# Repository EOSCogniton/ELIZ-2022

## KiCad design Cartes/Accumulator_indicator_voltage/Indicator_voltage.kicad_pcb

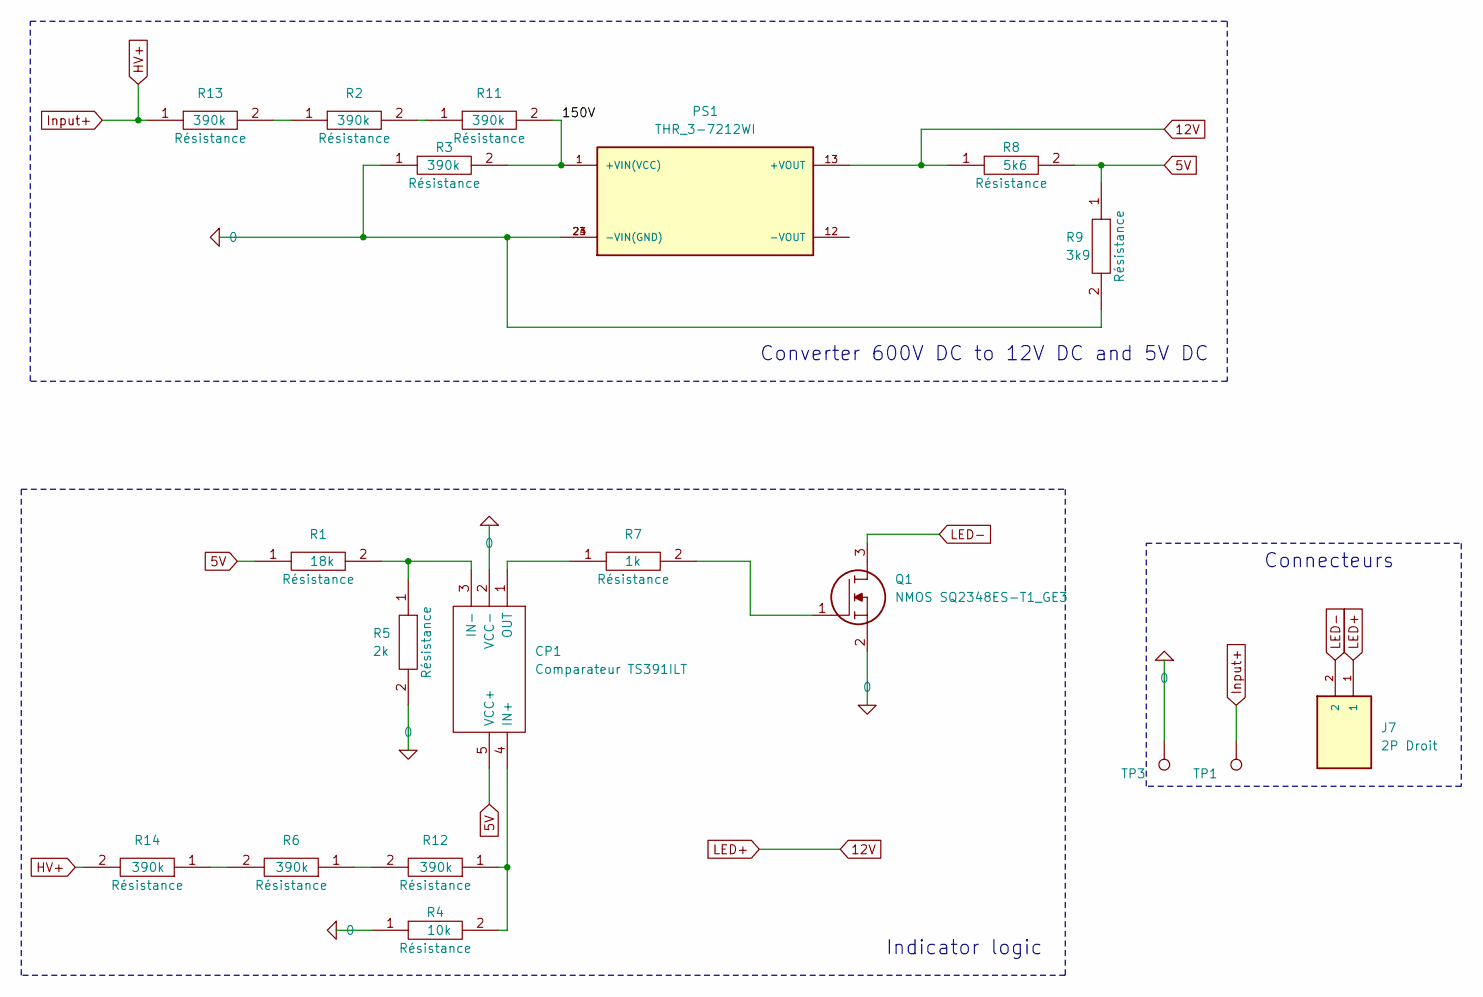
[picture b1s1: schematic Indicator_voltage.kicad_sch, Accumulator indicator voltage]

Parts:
CP1: Comparateur TS391ILT; SOT95P280X145-5N; Manufacturer_Part_Number TS391ILT; Mouser Part Number 511-TS391IL
J7: 2P Droit 2-11-2022; MOLEX_22-11-2022; PARTREV BD8
PS1: THR_3-7212WI; CONV_THR_3-7212WI; PARTREV July 21, 2021
Q1: NMOS SQ2348ES-T1_GE3; SOT95P237X112-3N; Manufacturer_Part_Number SQ2348ES-T1_GE3; Mouser Part Number 781-SQ2348ES-T1_GE3
R1: 18k; RESC3216X70N; Manufacturer_Part_Number RK73H2BLTDD2152F; Mouser Part Number N/A
R2, R3, R6, R11, R12, R13, R14: 390k; RESC3216X70N; Manufacturer_Part_Number RK73H2BLTDD2152F; Mouser Part Number N/A
R4: 10k; RESC3216X70N; Manufacturer_Part_Number RK73H2BLTDD2152F; Mouser Part Number N/A
R5: 2k; RESC3216X70N; Manufacturer_Part_Number RK73H2BLTDD2152F; Mouser Part Number N/A
R7: 1k; RESC3216X70N; Manufacturer_Part_Number RK73H2BLTDD2152F; Mouser Part Number N/A
R8: 5k6; RESC3216X70N; Manufacturer_Part_Number RK73H2BLTDD2152F; Mouser Part Number N/A
R9: 3k9; RESC3216X70N; Manufacturer_Part_Number RK73H2BLTDD2152F; Mouser Part Number N/A
TP1, TP3: type="R" model="TestPoint" lib=""; SolderWire-2.5sqmm_1x01_D2.4mm_OD3.6mm

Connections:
0: CP1.2 (VCC-), PS1.23 (-VIN(GND)), PS1.24 (-VIN(GND)), Q1.2, R3.1, R4.1, R5.2, R9.2, TP3.1
5V: CP1.5 (VCC+), R1.1, R8.2, R9.1
12V: J7.1, PS1.13 (+VOUT), R8.1
/150V: PS1.1 (+VIN(VCC)), R3.2, R11.2
HV+: R13.1, R14.2, TP1.1
LED-: J7.2, Q1.3
unnamed: CP1.4 (IN+), R4.2, R12.1
unnamed: CP1.3 (IN-), R1.2, R5.1
unnamed: CP1.1 (OUT), R7.1
unnamed: Q1.1, R7.2
unnamed: R2.2, R11.1
unnamed: R6.1, R12.2
unnamed: R2.1, R13.2
unnamed: R6.2, R14.1

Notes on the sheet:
Indicator logic
Connecteurs
Converter 600V DC to 12V DC and 5V DC

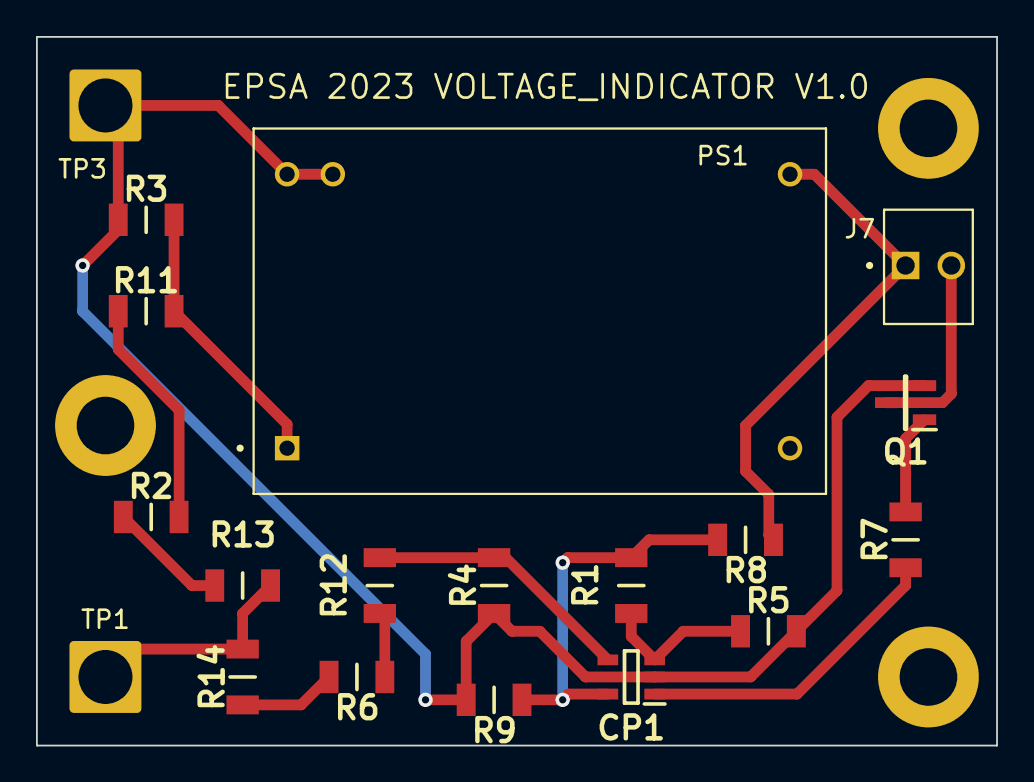
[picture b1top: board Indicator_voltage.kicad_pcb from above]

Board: 2 copper layers, 53.3 x 39.4 mm, 19 parts (0 on the bottom side), 14 nets.

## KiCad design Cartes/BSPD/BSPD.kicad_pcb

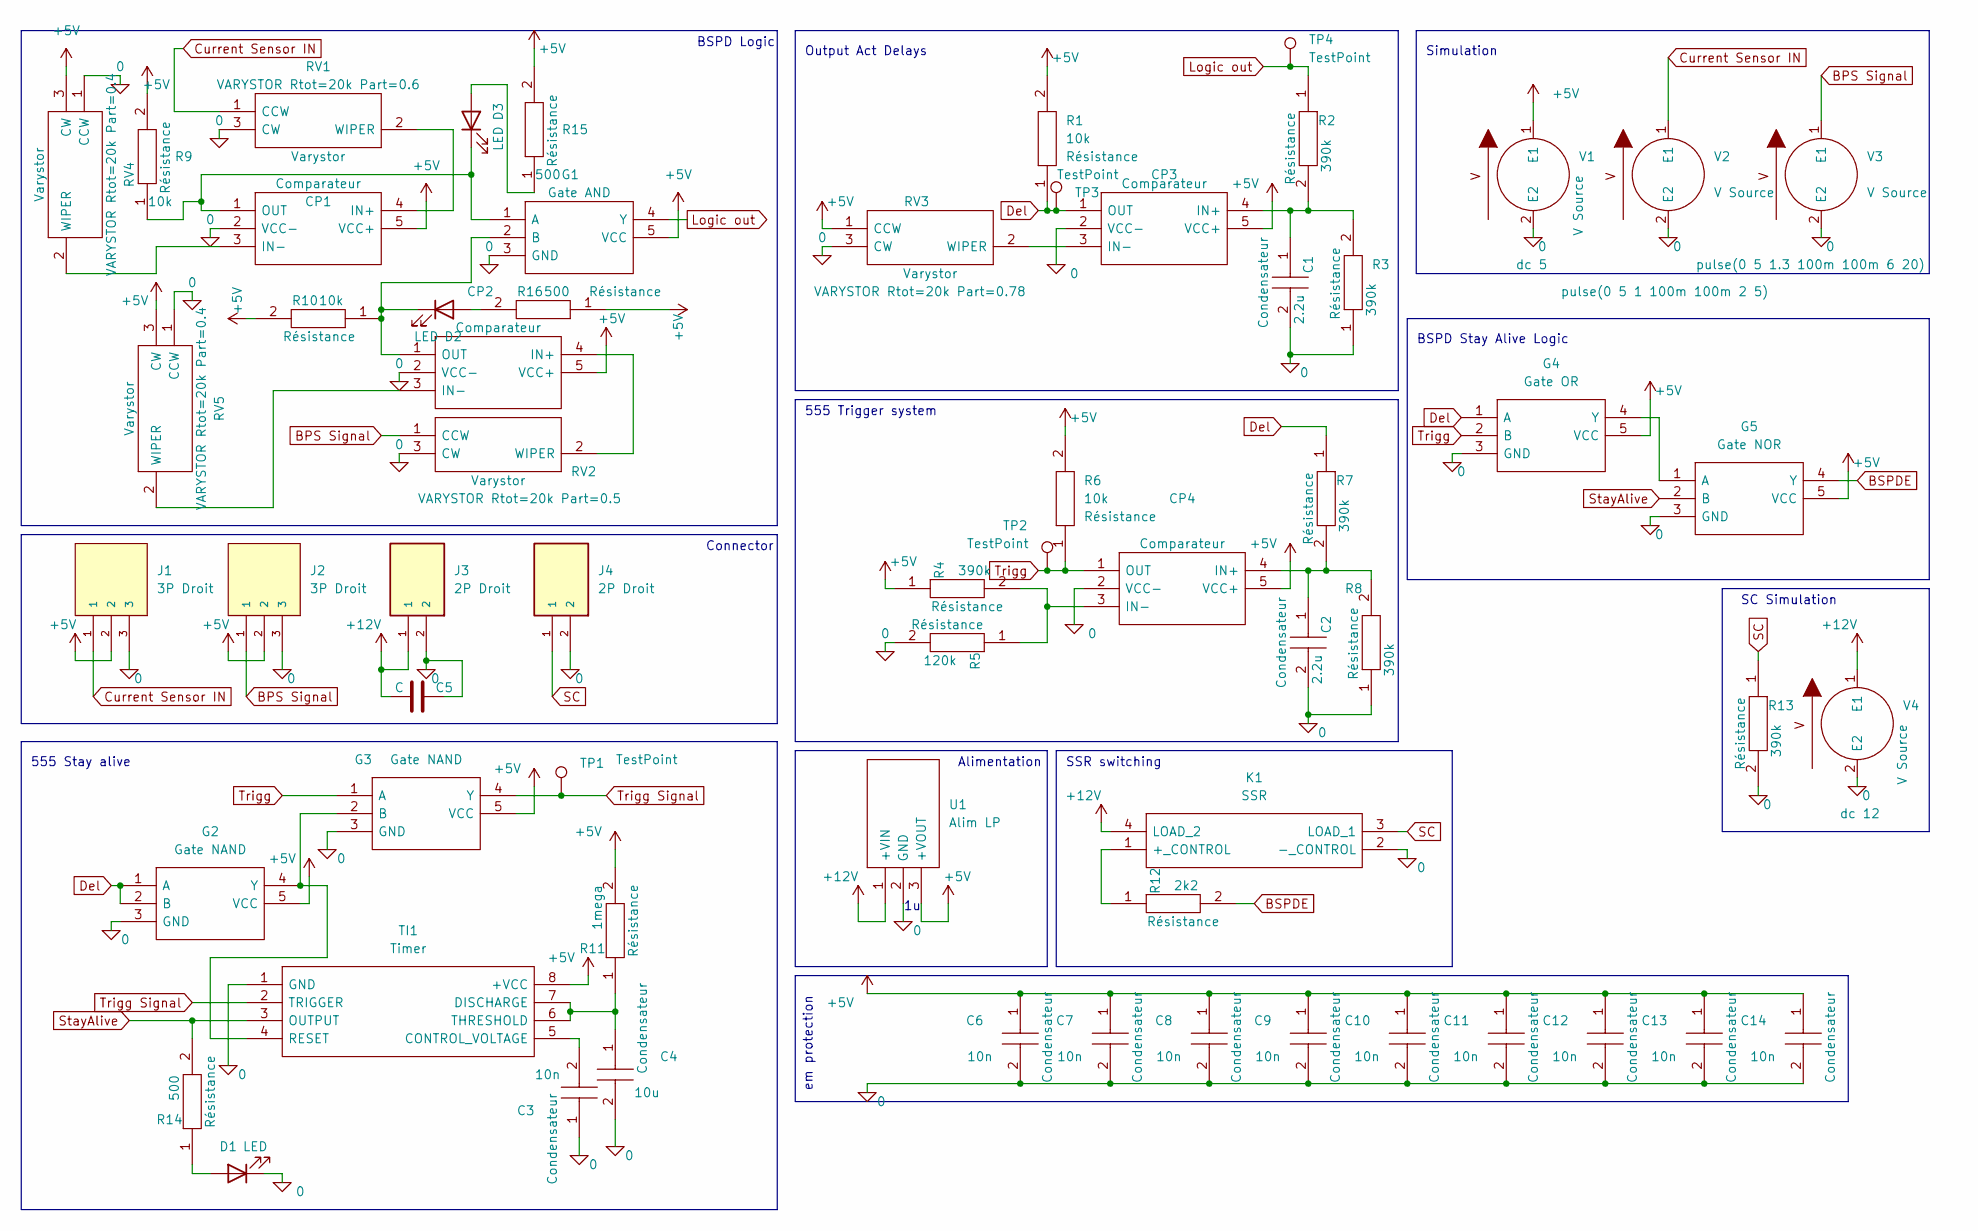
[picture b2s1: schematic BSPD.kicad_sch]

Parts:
C1, C2, C3, C4, C6, C7, C8, C9, C10, C11, C12, C13, C14: Condensateur 0805Y1000104JXT; CAPC2012X130N; Manufacturer_Part_Number 0805Y1000104JXT
C5: C; CP_Radial_D5.0mm_P2.00mm
CP1, CP2, CP3, CP4: Comparateur TS391ILT; SOT95P280X145-5N; Manufacturer_Part_Number TS391ILT; Mouser Part Number 511-TS391IL
D1, D2, D3: LED; LED_D5.0mm
G1: Gate AND SN74AHCT1G08DBVR; SOT95P280X145-5N; Manufacturer_Part_Number SN74AHCT1G08DBVR; Mouser Part Number 595-SN74AHCT1G08DBVR
G2, G3: Gate NAND SN74AHCT1G00DBVR; SOT95P280X145-5N; Manufacturer_Part_Number SN74AHCT1G00DBVR; Mouser Part Number 595-SN74AHCT1G00DBVR
G4: Gate OR SN74AHCT1G32DBVR; SOT95P280X145-5N; Manufacturer_Part_Number SN74AHCT1G32DBVR; Mouser Part Number 595-SN74AHCT1G32DBVR
G5: Gate NOR SN74AHCT1G02DBVR; SOT95P280X145-5N; Manufacturer_Part_Number SN74AHCT1G02DBVR; Mouser Part Number 595-SN74AHCT1G02DBVR
J1, J2: 3P Droit 22-11-2032; MOLEX_22-11-2032; PARTREV BD8
J3, J4: 2P Droit 2-11-2022; MOLEX_22-11-2022; PARTREV BD8
K1: SSR CPC1394GR; CPC1394GR; Manufacturer_Part_Number CPC1394GR; Mouser Part Number 849-CPC1394GR
R1, R2, R3, R4, R5, R6, R7, R8, R9, R10, R11, R12, R13, R14, R15, R16: Résistance RK73H2BLTDD2152F; RESC3216X70N; Manufacturer_Part_Number RK73H2BLTDD2152F; Mouser Part Number N/A
RV1, RV2, RV3, RV4, RV5: Varystor 3296Y-1-223LF; 3296Y1223LF; Manufacturer_Part_Number 3296Y-1-223LF; Mouser Part Number 652-3296Y-1-223LF
TI1: Timer 555 LM555CMX_NOPB; DIP-8_W7.62mm_Socket; Manufacturer_Part_Number LM555CMX/NOPB; Mouser Part Number 926-LM555CMX/NOPB
TP1, TP2, TP3, TP4: TestPoint; TestPoint_Pad_D2.0mm
U1: Alim LP TSR_0.5-2450; TSR-0.5-2433; Manufacturer_Part_Number TSR 0.5-2450; Mouser Part Number 495-TSR0.5-2450
V1, V2, V3, V4: VSOURCE

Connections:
0: C1.2, C2.2, C3.1, C4.2, C5.2, C6.2, C7.2, C8.2, C9.2, C10.2, C11.2, C12.2, C13.2, C14.2, CP1.2 (VCC-), CP2.2 (VCC-), CP3.2 (VCC-), CP4.2 (VCC-), D1.1 (K), G1.3 (GND), G2.3 (GND), G3.3 (GND), G4.3 (GND), G5.3 (GND), J1.3, J2.3, J3.2, J4.2, K1.2 (-_CONTROL), R3.1, R5.2, R8.1, R13.2, RV1.3 (CW), RV2.3 (CW), RV3.3 (CW), RV4.1 (CCW), RV5.1 (CCW), TI1.1 (GND), U1.2 (GND), V1.2 (E2), V2.2 (E2), V3.2 (E2), V4.2 (E2)
+5V: C6.1, C7.1, C8.1, C9.1, C10.1, C11.1, C12.1, C13.1, C14.1, CP1.5 (VCC+), CP2.5 (VCC+), CP3.5 (VCC+), CP4.5 (VCC+), G1.5 (VCC), G2.5 (VCC), G3.5 (VCC), G4.5 (VCC), G5.5 (VCC), J1.2, J2.2, R1.2, R4.1, R6.2, R9.2, R10.2, R11.2, R15.2, R16.1, RV3.1 (CCW), RV4.3 (CW), RV5.3 (CW), TI1.8 (+VCC), U1.3 (+VOUT), V1.1 (E1)
+12V: C5.1, J3.1, K1.4 (LOAD_2), U1.1 (+VIN), V4.1 (E1)
BPS Signal: J2.1, RV2.1 (CCW), V3.1 (E1)
BSPDE: G5.4 (Y), R12.2
Current Sensor IN: J1.1, RV1.1 (CCW), V2.1 (E1)
Del: CP3.1 (OUT), G2.1 (A), G2.2 (B), G4.1 (A), R1.1, R7.1, TP3.1
Logic out: G1.4 (Y), R2.1, TP4.1
unnamed: C1.1, CP3.4 (IN+), R2.2, R3.2
unnamed: C2.1, CP4.4 (IN+), R7.2, R8.2
unnamed: C3.2, TI1.5 (CONTROL_VOLTAGE)
unnamed: C4.1, R11.1, TI1.6 (THRESHOLD), TI1.7 (DISCHARGE)
unnamed: CP1.1 (OUT), D3.1 (K), G1.1 (A), R9.1
unnamed: CP1.3 (IN-), RV4.2 (WIPER)
unnamed: CP1.4 (IN+), RV1.2 (WIPER)
unnamed: CP2.1 (OUT), D2.1 (K), G1.2 (B), R10.1
unnamed: CP2.3 (IN-), RV5.2 (WIPER)
unnamed: CP2.4 (IN+), RV2.2 (WIPER)
unnamed: CP3.3 (IN-), RV3.2 (WIPER)
unnamed: CP4.3 (IN-), R4.2, R5.1
unnamed: D1.2 (A), R14.1
unnamed: D2.2 (A), R16.2
unnamed: D3.2 (A), R15.1
unnamed: G2.4 (Y), G3.2 (B), TI1.4 (RESET)
unnamed: G4.4 (Y), G5.1 (A)
unnamed: K1.1 (+_CONTROL), R12.1
SC: J4.1, K1.3 (LOAD_1), R13.1
StayAlive: G5.2 (B), R14.2, TI1.3 (OUTPUT)
Trigg: CP4.1 (OUT), G3.1 (A), G4.2 (B), R6.1, TP2.1
Trigg Signal: G3.4 (Y), TI1.2 (TRIGGER), TP1.1

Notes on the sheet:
em protection
BSPD Stay Alive Logic
SSR switching
Simulation
Connector
BSPD Logic
555 Trigger system
SC Simulation
Output Act Delays
555 Stay alive
Alimentation

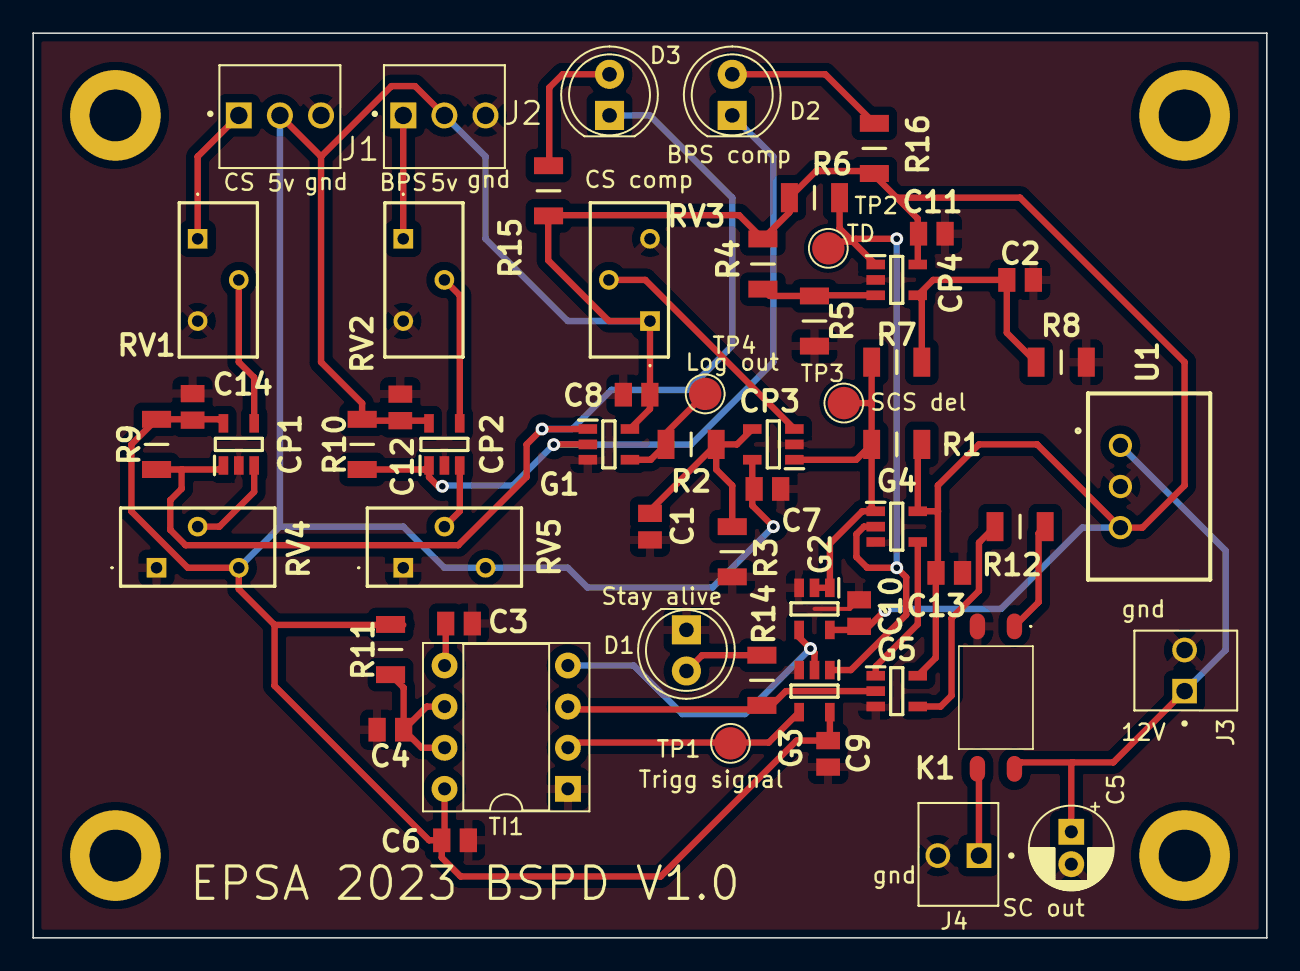
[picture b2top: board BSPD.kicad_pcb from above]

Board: 2 copper layers, 76.2 x 55.9 mm, 57 parts (0 on the bottom side), 30 nets.

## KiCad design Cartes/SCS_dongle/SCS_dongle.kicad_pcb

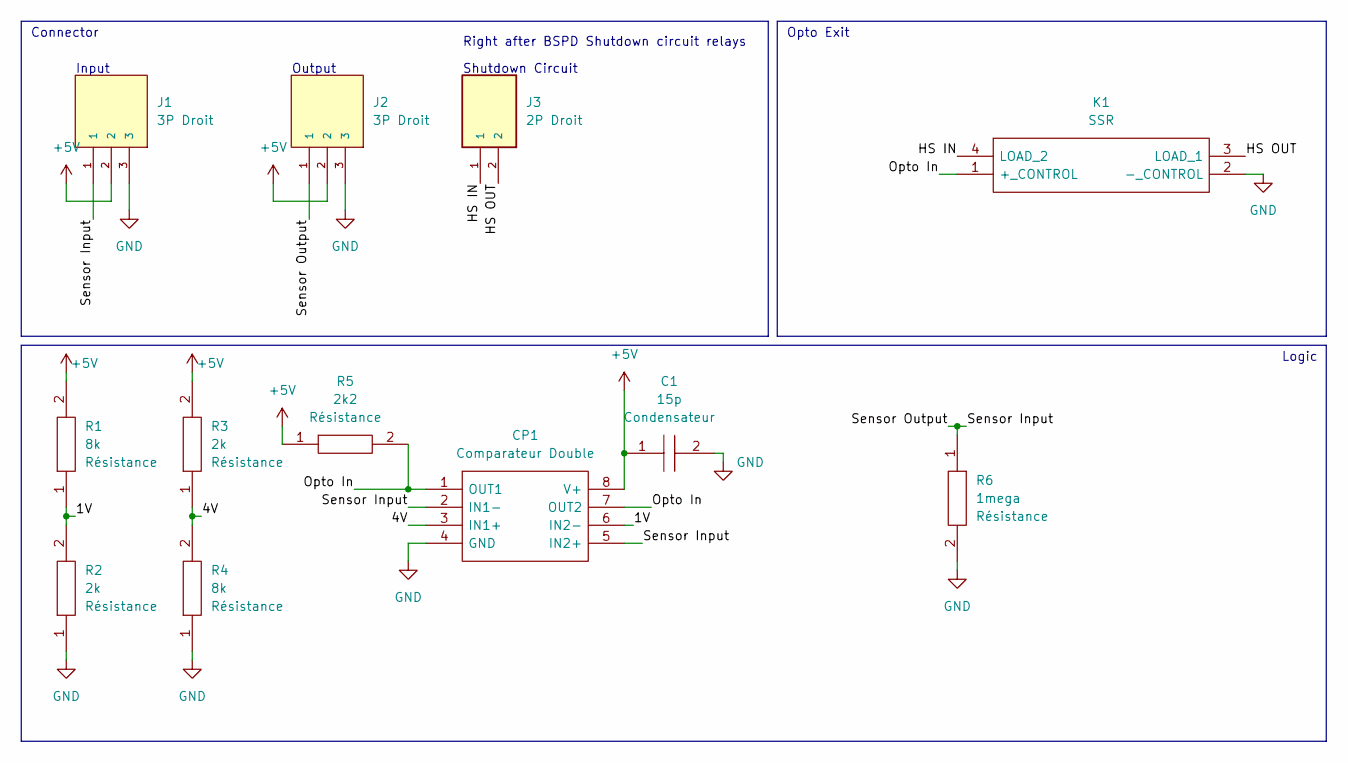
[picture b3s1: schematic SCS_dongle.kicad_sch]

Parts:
C1: Condensateur 0805Y1000104JXT; CAPC2012X130N; Manufacturer_Part_Number 0805Y1000104JXT
CP1: Comparateur Double LM393LVDR; SOIC127P600X175-8N; Manufacturer_Part_Number LM393LVDR; Mouser Part Number 595-LM393LVDR
J1, J2: 3P Droit 22-11-2032; MOLEX_22-11-2032; PARTREV BD8
J3: 2P Droit 2-11-2022; MOLEX_22-11-2022; PARTREV BD8
K1: SSR CPC1394GR; CPC1394GR; Manufacturer_Part_Number CPC1394GR; Mouser Part Number 849-CPC1394GR
R1, R2, R3, R4, R5, R6: Résistance RK73H2BLTDD2152F; RESC3216X70N; Manufacturer_Part_Number RK73H2BLTDD2152F; Mouser Part Number N/A

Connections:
+5V: C1.1, CP1.8 (V+), J1.2, J2.2, R1.2, R3.2, R5.1
/1V: CP1.6 (IN2-), R1.1, R2.2
/4V: CP1.3 (IN1+), R3.1, R4.2
/HS IN: J3.1, K1.4 (LOAD_2)
/HS OUT: J3.2, K1.3 (LOAD_1)
/Opto In: CP1.1 (OUT1), CP1.7 (OUT2), K1.1 (+_CONTROL), R5.2
/Sensor Input: CP1.2 (IN1-), CP1.5 (IN2+), J1.1, J2.1, R6.1
GND: C1.2, CP1.4 (GND), J1.3, J2.3, K1.2 (-_CONTROL), R2.1, R4.1, R6.2

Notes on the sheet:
Connector
Logic
Right after BSPD Shutdown circuit relays
Opto Exit
Output
Input
Shutdown Circuit

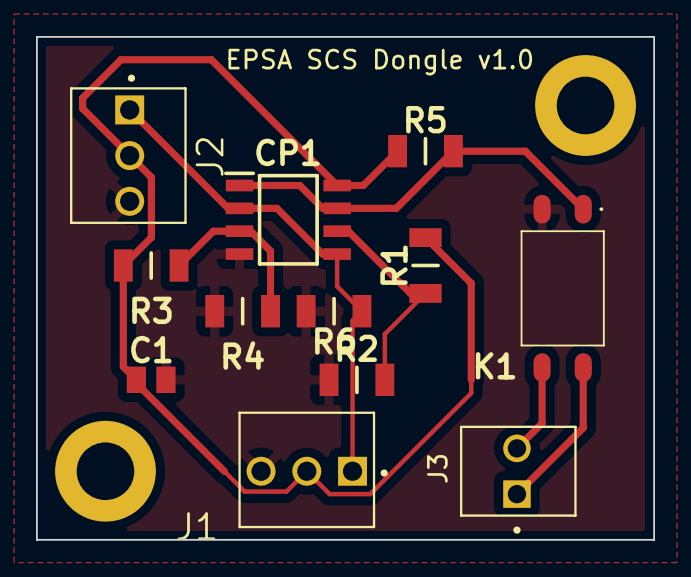
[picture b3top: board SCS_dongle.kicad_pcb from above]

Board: 2 copper layers, 34.3 x 27.9 mm, 12 parts (0 on the bottom side), 8 nets.

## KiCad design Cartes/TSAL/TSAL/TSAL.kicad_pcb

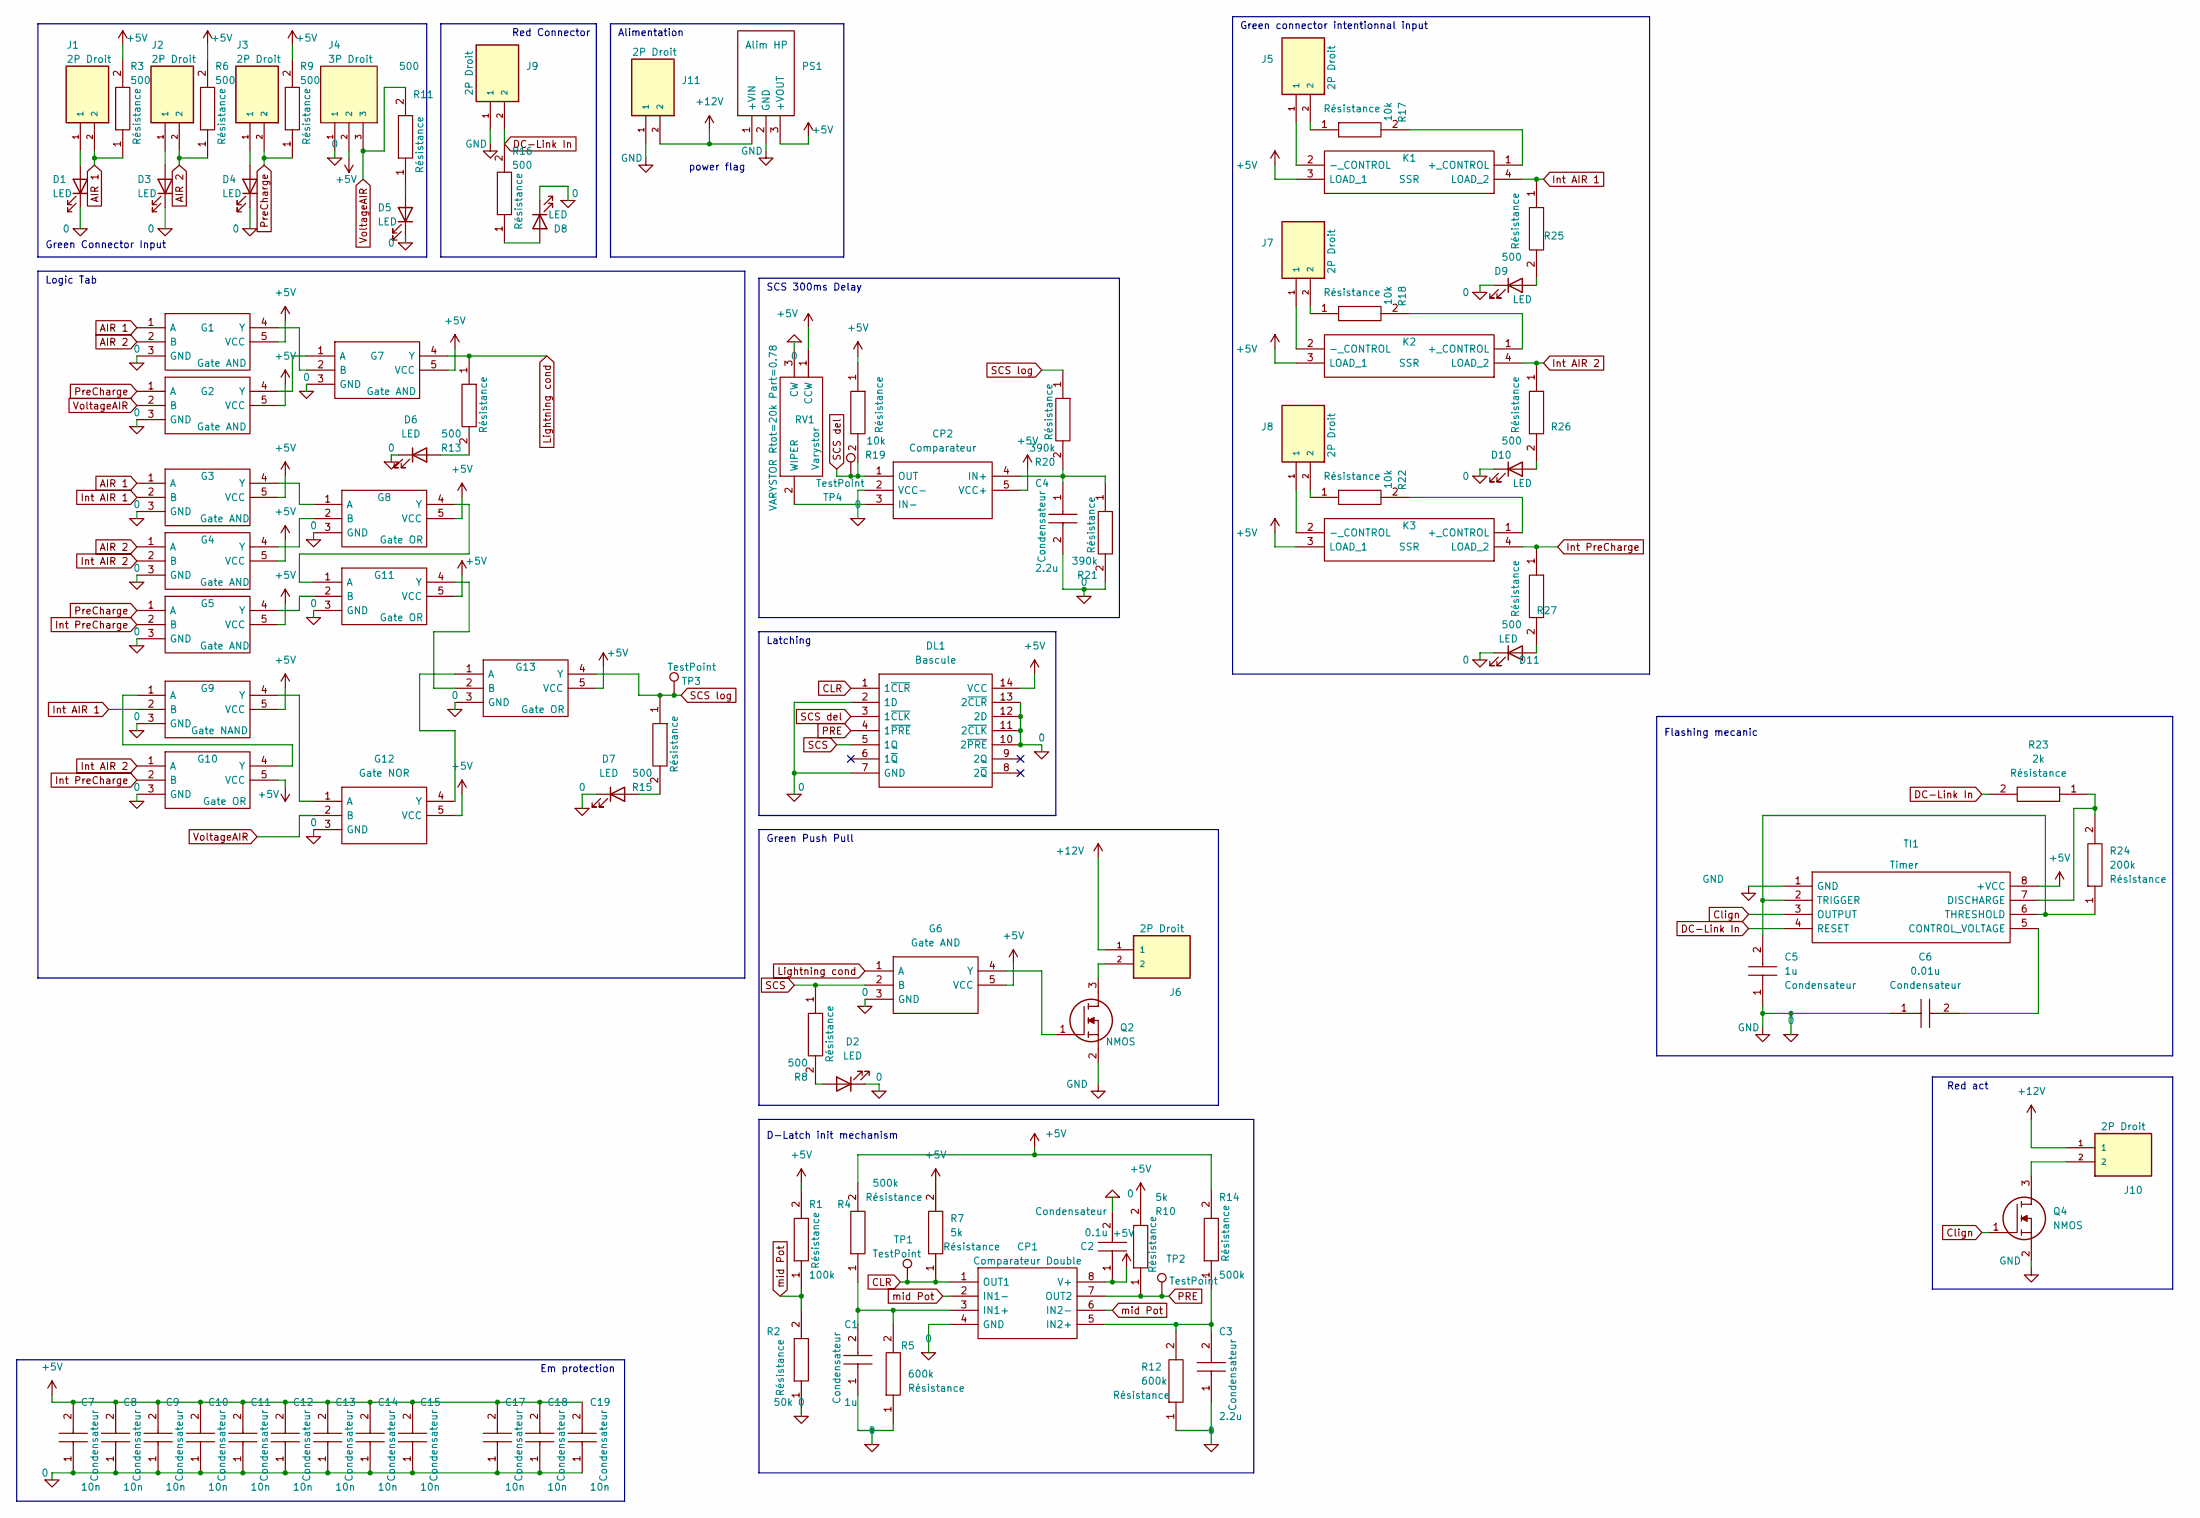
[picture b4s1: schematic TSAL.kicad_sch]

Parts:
C1, C2, C3, C4, C5, C6, C7, C8, C9, C10, C11, C12, C13, C14, C15, C17, C18, C19: Condensateur 0805Y1000104JXT; CAPC2012X130N; Manufacturer_Part_Number 0805Y1000104JXT
CP1: Comparateur Double LM393LVDR; SOIC127P600X175-8N; Manufacturer_Part_Number LM393LVDR; Mouser Part Number 595-LM393LVDR
CP2: Comparateur TS391ILT; SOT95P280X145-5N; Manufacturer_Part_Number TS391ILT; Mouser Part Number 511-TS391IL
D1, D2, D3, D4, D5, D6, D7, D8, D9, D10, D11: LED; LED_D5.0mm
DL1: Bascule D SN74HCS72QDRQ1; SOIC127P600X175-14N; Manufacturer_Part_Number SN74HCS72QDRQ1; Mouser Part Number 595-SN74HCS72QDRQ1
G1, G2, G3, G4, G5, G6, G7: Gate AND SN74AHCT1G08DBVR; SOT95P280X145-5N; Manufacturer_Part_Number SN74AHCT1G08DBVR; Mouser Part Number 595-SN74AHCT1G08DBVR
G8, G10, G11, G13: Gate OR SN74AHCT1G32DBVR; SOT95P280X145-5N; Manufacturer_Part_Number SN74AHCT1G32DBVR; Mouser Part Number 595-SN74AHCT1G32DBVR
G9: Gate NAND SN74AHCT1G00DBVR; SOT95P280X145-5N; Manufacturer_Part_Number SN74AHCT1G00DBVR; Mouser Part Number 595-SN74AHCT1G00DBVR
G12: Gate NOR SN74AHCT1G02DBVR; SOT95P280X145-5N; Manufacturer_Part_Number SN74AHCT1G02DBVR; Mouser Part Number 595-SN74AHCT1G02DBVR
J1, J2, J3, J5, J6, J7, J8, J9, J10, J11: 2P Droit 2-11-2022; MOLEX_22-11-2022; PARTREV BD8
J4: 3P Droit 22-11-2032; MOLEX_22-11-2032; PARTREV BD8
K1, K2, K3: SSR CPC1394GR; CPC1394GR; Manufacturer_Part_Number CPC1394GR; Mouser Part Number 849-CPC1394GR
PS1: Alim HP TSR_2-2450; TSR-2; Manufacturer_Part_Number TSR 2-2450; Mouser Part Number 495-TSR2-2450
Q2, Q4: NMOS SQ2348ES-T1_GE3; SOT95P237X112-3N; Manufacturer_Part_Number SQ2348ES-T1_GE3; Mouser Part Number 781-SQ2348ES-T1_GE3
R1, R2, R3, R4, R5, R6, R7, R8, R9, R10, R11, R12, R13, R14, R15, R16, R17, R18, R19, R20, R21, R22, R23, R24, R25, R26, R27: Résistance RK73H2BLTDD2152F; RESC3216X70N; Manufacturer_Part_Number RK73H2BLTDD2152F; Mouser Part Number N/A
RV1: Varystor 3296Y-1-223LF; 3296Y1223LF; Manufacturer_Part_Number 3296Y-1-223LF; Mouser Part Number 652-3296Y-1-223LF
TI1: Timer 555 LM555CMX_NOPB; SOIC127P600X175-8N; Manufacturer_Part_Number LM555CMX/NOPB; Mouser Part Number 926-LM555CMX/NOPB
TP1, TP2, TP3, TP4: TestPoint; TestPoint_Pad_D2.0mm

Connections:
0: C1.1, C2.2, C3.1, C4.2, C5.1, C6.1, C7.1, C8.1, C9.1, C10.1, C11.1, C12.1, C13.1, C14.1, C15.1, C17.1, C18.1, C19.1, CP1.4 (GND), CP2.2 (VCC-), D1.1 (K), D2.1 (K), D3.1 (K), D4.1 (K), D5.1 (K), D6.1 (K), D7.1 (K), D8.1 (K), D9.1 (K), D10.1 (K), D11.1 (K), DL1.2 (1D), DL1.7 (GND), DL1.10 (2~PRE), DL1.11 (2~CLK), DL1.12 (2D), DL1.13 (2~CLR), G1.3 (GND), G2.3 (GND), G3.3 (GND), G4.3 (GND), G5.3 (GND), G6.3 (GND), G7.3 (GND), G8.3 (GND), G9.3 (GND), G10.3 (GND), G11.3 (GND), G12.3 (GND), G13.3 (GND), J4.1, J9.1, J11.1, PS1.2 (GND), Q2.2, Q4.2, R2.1, R5.1, R12.1, R21.2, RV1.3 (CW), TI1.1 (GND)
+5V: C2.1, C7.2, C8.2, C9.2, C10.2, C11.2, C12.2, C13.2, C14.2, C15.2, C17.2, C18.2, C19.2, CP1.8 (V+), CP2.5 (VCC+), DL1.14 (VCC), G1.5 (VCC), G2.5 (VCC), G3.5 (VCC), G4.5 (VCC), G5.5 (VCC), G6.5 (VCC), G7.5 (VCC), G8.5 (VCC), G9.5 (VCC), G10.5 (VCC), G11.5 (VCC), G12.5 (VCC), G13.5 (VCC), J4.2, K1.3 (LOAD_1), K2.3 (LOAD_1), K3.3 (LOAD_1), PS1.3 (+VOUT), R1.2, R3.2, R4.2, R6.2, R7.2, R9.2, R10.2, R14.2, R19.1, RV1.1 (CCW), TI1.8 (+VCC)
+12V: J6.1, J10.1, J11.2, PS1.1 (+VIN)
AIR 1: G1.1 (A), G3.1 (A), J1.2, R3.1
AIR 2: G1.2 (B), G4.1 (A), J2.2, R6.1
CLR: CP1.1 (OUT1), DL1.1 (1~CLR), R7.1, TP1.1
Clign: Q4.1, TI1.3 (OUTPUT)
DC-Link In: J9.2, R16.2, R23.2, TI1.4 (RESET)
Int AIR 1: G3.2 (B), G9.2 (B), K1.4 (LOAD_2), R25.1
Int AIR 2: G4.2 (B), G10.1 (A), K2.4 (LOAD_2), R26.1
Int PreCharge: G5.2 (B), G10.2 (B), K3.4 (LOAD_2), R27.1
Lightning cond: G6.1 (A), G7.4 (Y), R13.1
unnamed: C1.2, CP1.3 (IN1+), R4.1, R5.2
unnamed: C3.2, CP1.5 (IN2+), R12.2, R14.1
unnamed: C4.1, CP2.4 (IN+), R20.2, R21.1
unnamed: C5.2, R24.1, TI1.2 (TRIGGER), TI1.6 (THRESHOLD)
unnamed: C6.2, TI1.5 (CONTROL_VOLTAGE)
unnamed: CP2.3 (IN-), RV1.2 (WIPER)
unnamed: D1.2 (A), J1.1
unnamed: D2.2 (A), R8.2
unnamed: D3.2 (A), J2.1
unnamed: D4.2 (A), J3.1
unnamed: D5.2 (A), R11.1
unnamed: D6.2 (A), R13.2
unnamed: D7.2 (A), R15.2
unnamed: D8.2 (A), R16.1
unnamed: D9.2 (A), R25.2
unnamed: D10.2 (A), R26.2
unnamed: D11.2 (A), R27.2
unnamed: G1.4 (Y), G7.2 (B)
unnamed: G2.4 (Y), G7.1 (A)
unnamed: G3.4 (Y), G8.1 (A)
unnamed: G4.4 (Y), G8.2 (B)
unnamed: G5.4 (Y), G11.2 (B)
unnamed: G6.4 (Y), Q2.1
unnamed: G8.4 (Y), G11.1 (A)
unnamed: G9.1 (A), G10.4 (Y)
unnamed: G11.4 (Y), G13.2 (B)
unnamed: G9.4 (Y), G12.1 (A)
unnamed: G12.4 (Y), G13.1 (A)
unnamed: J5.1, K1.2 (-_CONTROL)
unnamed: J5.2, R17.1
unnamed: J6.2, Q2.3
unnamed: J7.1, K2.2 (-_CONTROL)
unnamed: J7.2, R18.1
unnamed: J8.1, K3.2 (-_CONTROL)
unnamed: J8.2, R22.1
unnamed: J10.2, Q4.3
unnamed: K1.1 (+_CONTROL), R17.2
unnamed: K2.1 (+_CONTROL), R18.2
unnamed: K3.1 (+_CONTROL), R22.2
unnamed: R23.1, R24.2, TI1.7 (DISCHARGE)
PRE: CP1.7 (OUT2), DL1.4 (1~PRE), R10.1, TP2.1
PreCharge: G2.1 (A), G5.1 (A), J3.2, R9.1
SCS: DL1.5 (1Q), G6.2 (B), R8.1
SCS del: CP2.1 (OUT), DL1.3 (1~CLK), R19.2, TP4.1
SCS log: G13.4 (Y), R15.1, R20.1, TP3.1
VoltageAIR: G2.2 (B), G12.2 (B), J4.3, R11.2
mid Pot: CP1.2 (IN1-), CP1.6 (IN2-), R1.1, R2.2

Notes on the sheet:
Green Push Pull
Red Connector
Flashing mecanic
power flag
Green Connector Input
Latching
Em protection
Green connector intentionnal input
Alimentation
Red act
Logic Tab
SCS 300ms Delay
D-Latch init mechanism

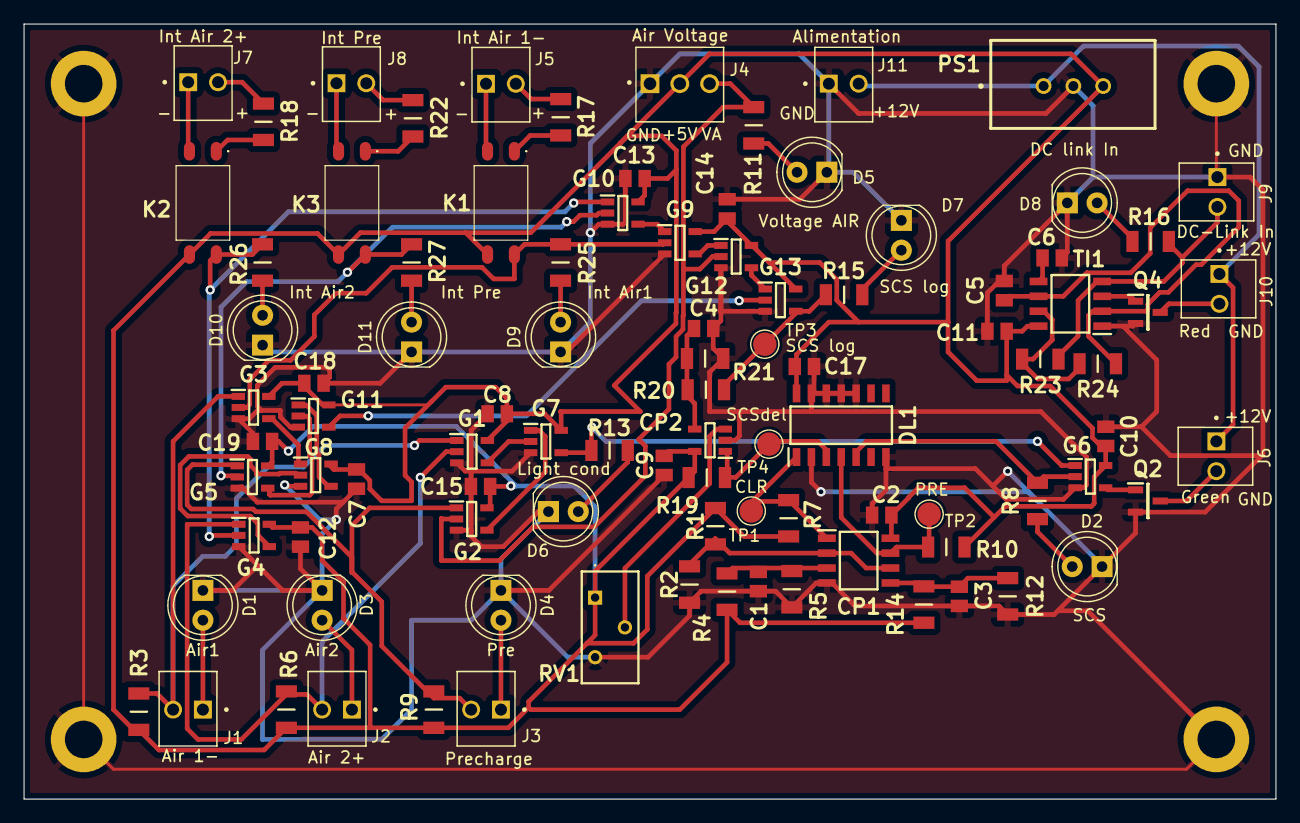
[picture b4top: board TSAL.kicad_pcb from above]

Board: 2 copper layers, 106.7 x 66.0 mm, 95 parts (0 on the bottom side), 59 nets.

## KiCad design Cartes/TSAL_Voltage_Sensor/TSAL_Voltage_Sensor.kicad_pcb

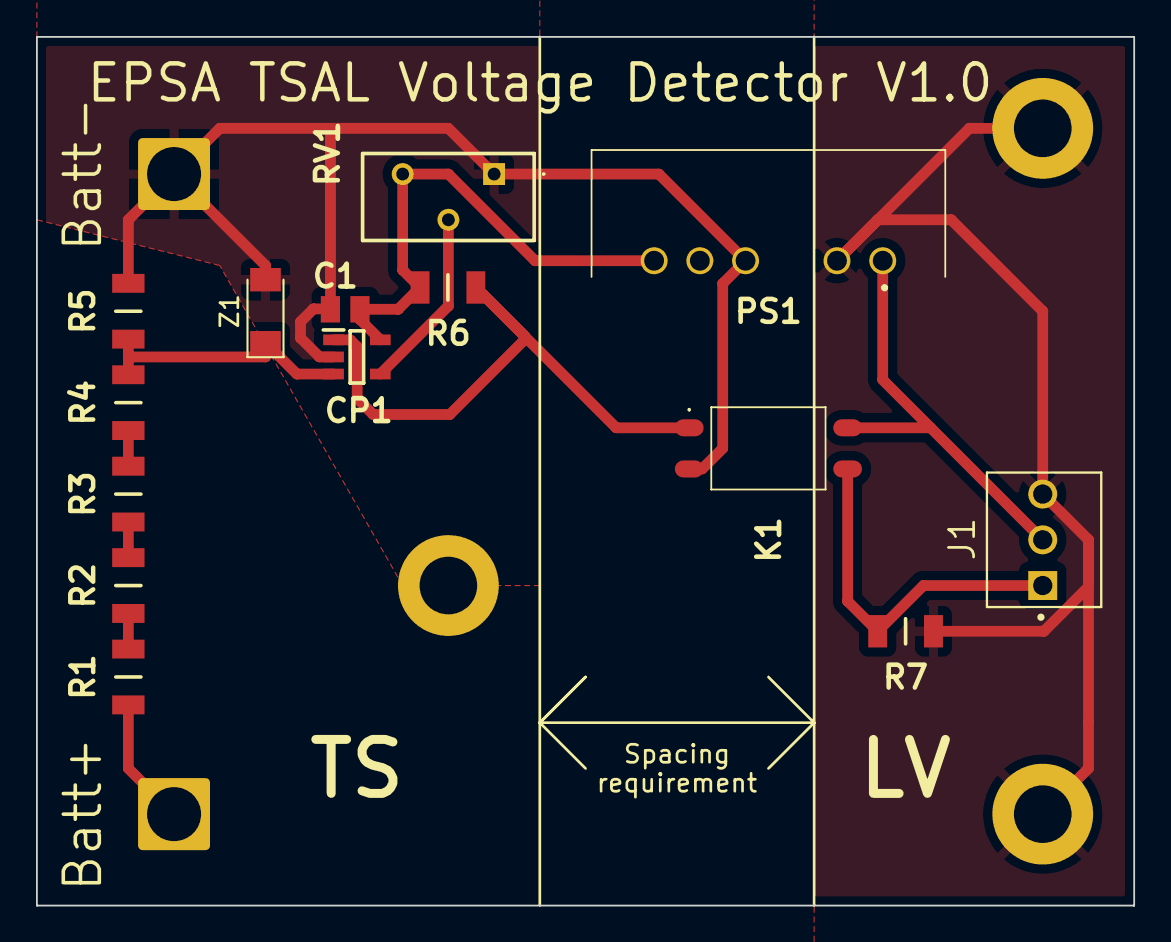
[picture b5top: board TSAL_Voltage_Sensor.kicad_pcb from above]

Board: 2 copper layers, 61.0 x 48.3 mm, 16 parts (0 on the bottom side), 12 nets.

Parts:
C1: Condensateur 0805Y1000104JXT; CAPC2012X130N
CP1: Comparateur TS391ILT; SOT95P280X145-5N
J1: 3P Droit 22-11-2032; MOLEX_22-11-2032
K1: SSR CPC1394GR; CPC1394GR
PS1: Alim Iso PDM2-S5-S5-S; PDM2S5S5S
R1, R2, R3, R4, R5, R6, R7: Résistance RK73H2BLTDD2152F; RESC3216X70N
RV1: Varystor 3296Y-1-223LF; 3296Y1223LF
TP1, TP2: TestPoint; SolderWire-2.5sqmm_1x01_D2.4mm_OD3.6mm
Z1: Zener TZM5224B-GS08; D_MiniMELF

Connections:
0: C1.1, CP1.2 (VCC-), K1.2 (-_CONTROL), PS1.4 (0V), R5.1, RV1.1 (CCW), TP2.1, Z1.2
+5V: C1.2, CP1.5 (VCC+), PS1.6 (+VO), R6.2, RV1.3 (CW)
+5VA: J1.2, K1.4 (LOAD_2), PS1.1 (VIN)
+BATT: R1.2, TP1.1
Comp: CP1.1 (OUT), K1.1 (+_CONTROL), R6.1
Exit: J1.1, K1.3 (LOAD_1), R7.2
GND: J1.3, PS1.2 (GND), R7.1
unnamed: R1.1, R2.1
unnamed: R2.2, R3.2
unnamed: R3.1, R4.1
unnamed: CP1.3 (IN-), R4.2, R5.2, Z1.1
unnamed: CP1.4 (IN+), RV1.2 (WIPER)
